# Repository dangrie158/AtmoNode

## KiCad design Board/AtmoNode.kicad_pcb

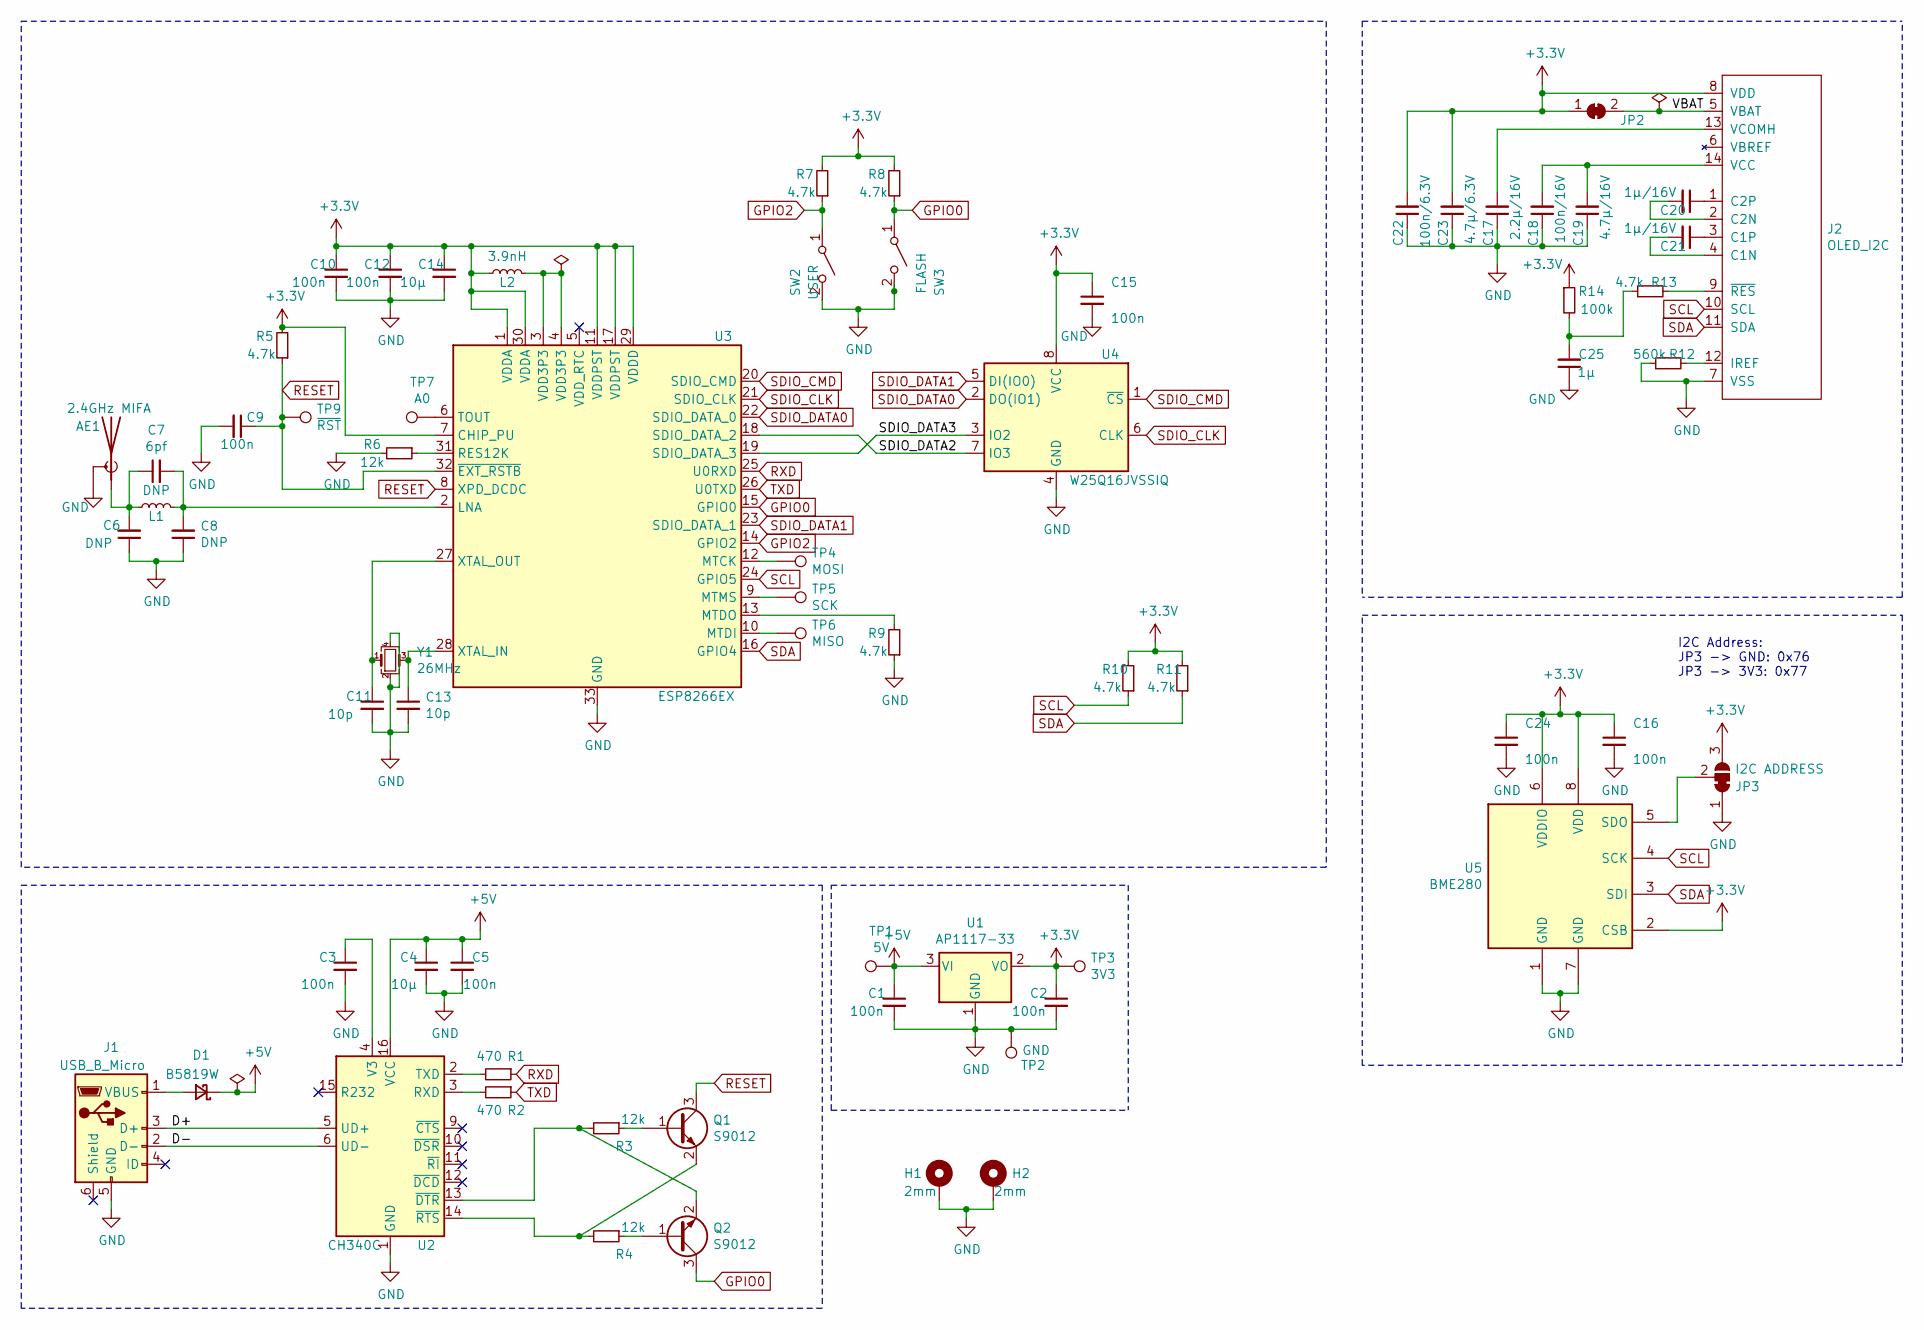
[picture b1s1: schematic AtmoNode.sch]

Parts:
AE1: 2.4GHz MIFA; Texas_SWRA117D_2.4GHz_Right
C1, C2, C3, C5, C9, C10, C12, C15, C16, C24: 100n; C_0402_1005Metric
C4, C14: 10µ; C_0805_2012Metric
C6, C8: DNP; C_0402_1005Metric
C7: 6pf; C_0402_1005Metric
C11, C13: 10p; C_0402_1005Metric
C17: 2.2µ/16V; C_0603_1608Metric
C18: 100n/16V; C_0402_1005Metric
C19: 4.7µ/16V; C_0603_1608Metric
C20, C21: 1µ/16V; C_0603_1608Metric
C22: 100n/6.3V; C_0402_1005Metric
C23: 4.7µ/6.3V; C_0603_1608Metric
C25: 1µ; C_0603_1608Metric
D1: B5819W; D_SOD-123
H1, H2: 2mm; MountingHole_2.2mm_M2_Pad_Via
J1: USB_B_Micro; USB_Micro-B_Amphenol_10118194_Horizontal
J2: OLED_I2C; WiseChip VG-6432TSWAG01
JP2: VDD-VBAT; SolderJumper-2_P1.3mm_Bridged_RoundedPad1.0x1.5mm
JP3: I2C ADDRESS; SolderJumper-3_P1.3mm_Bridged2Bar12_RoundedPad1.0x1.5mm
L1: DNP; L_0402_1005Metric_Pad0.77x0.64mm_HandSolder
L2: 3.9nH; L_0402_1005Metric_Pad0.77x0.64mm_HandSolder
Q1, Q2: S9012; SOT-23
R1, R2: 470; R_0402_1005Metric
R3, R4, R6: 12k; R_0402_1005Metric
R5, R7, R8, R9, R10, R11, R13: 4.7k; R_0402_1005Metric
R12: 560k; R_0603_1608Metric
R14: 100k; R_0402_1005Metric
SW2: USER; SW_SPST_CK_RS282G05A3
SW3: FLASH; SW_SPST_CK_RS282G05A3
TP1: 5V; TP1.0
TP2: GND; TP1.0
TP3: 3V3; TP1.0
TP4: MOSI; TP1.0
TP5: SCK; TP1.0
TP6: MISO; TP1.0
TP7: A0; TP1.0
TP9: ~RST; TP1.0
U1: AP1117-33; SOT-223-3_TabPin2
U2: CH340C; SOIC-16_3.9x9.9mm_P1.27mm
U3: ESP8266EX; QFN-32-1EP_5x5mm_P0.5mm_EP3.45x3.45mm
U4: W25Q16JVSSIQ; SOIC-8_5.23x5.23mm_P1.27mm
U5: BME280; Bosch_LGA-8_2.5x2.5mm_P0.65mm_ClockwisePinNumbering
Y1: 26MHz; Crystal_SMD_3225-4Pin_3.2x2.5mm

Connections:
+3V3: C2.1, C10.1, C12.1, C14.1, C15.1, C16.1, C22.2, C23.2, C24.1, J2.8 (VDD), JP2.1 (A), JP3.3 (B), L2.1, R5.2, R7.2, R8.2, R10.2, R11.2, R14.1, TP3.1, U1.2 (VO), U3.1 (VDDA), U3.7 (CHIP_PU), U3.11 (VDDPST), U3.17 (VDDPST), U3.29 (VDDD), U3.30 (VDDA), U4.8 (VCC), U5.2 (CSB), U5.6 (VDDIO), U5.8 (VDD)
+5V: C1.1, C4.1, C5.1, D1.1 (K), TP1.1, U1.3 (VI), U2.16 (VCC)
/D+: J1.3 (D+), U2.5 (UD+)
/D-: J1.2 (D-), U2.6 (UD-)
/SDIO_DATA2: U3.18 (SDIO_DATA_2), U4.7 (IO3)
/SDIO_DATA3: U3.19 (SDIO_DATA_3), U4.3 (IO2)
/VBAT: J2.5 (VBAT), JP2.2 (B)
GND: AE1.2 (Shield), C1.2, C2.2, C3.2, C4.2, C5.2, C6.1, C8.1, C9.2, C10.2, C11.2, C12.2, C13.2, C14.2, C15.2, C16.2, C17.1, C18.1, C19.1, C22.1, C23.1, C24.2, C25.1, H1.1, H2.1, J1.5 (GND), J2.7 (VSS), JP3.1 (A), R6.2, R9.1, R12.1, SW2.2 (B), SW3.2 (B), TP2.1, U1.1 (GND), U2.1 (GND), U3.33 (GND), U4.4 (GND), U5.1 (GND), U5.7 (GND), Y1.2, Y1.4
GPIO0: Q2.3 (C), R8.1, SW3.1 (A), U3.15 (GPIO0)
GPIO2: R7.1, SW2.1 (A), U3.14 (GPIO2)
unnamed: AE1.1 (A), C6.2, C7.1, L1.1
unnamed: C3.1, U2.4 (V3)
unnamed: C7.2, C8.2, L1.2, U3.2 (LNA)
unnamed: C11.1, U3.27 (XTAL_OUT), Y1.1
unnamed: C13.1, U3.28 (XTAL_IN), Y1.3
unnamed: C17.2, J2.13 (VCOMH)
unnamed: C18.2, C19.2, J2.14 (VCC)
unnamed: C20.1, J2.1 (C2P)
unnamed: C20.2, J2.2 (C2N)
unnamed: C21.1, J2.3 (C1P)
unnamed: C21.2, J2.4 (C1N)
unnamed: C25.2, R13.1, R14.2
unnamed: D1.2 (A), J1.1 (VBUS)
unnamed: J2.9 (~RES), R13.2
unnamed: J2.12 (IREF), R12.2
unnamed: JP3.2 (C), U5.5 (SDO)
unnamed: L2.2, U3.3 (VDD3P3), U3.4 (VDD3P3)
unnamed: Q1.1 (B), R3.1
unnamed: Q1.2 (E), R4.2, U2.14 (~RTS)
unnamed: Q2.1 (B), R4.1
unnamed: Q2.2 (E), R3.2, U2.13 (~DTR)
unnamed: R1.2, U2.2 (TXD)
unnamed: R2.2, U2.3 (RXD)
unnamed: R6.1, U3.31 (RES12K)
unnamed: R9.2, U3.13 (MTDO)
unnamed: TP4.1, U3.12 (MTCK)
unnamed: TP5.1, U3.9 (MTMS)
unnamed: TP6.1, U3.10 (MTDI)
unnamed: TP7.1, U3.6 (TOUT)
RESET: C9.1, Q1.3 (C), R5.1, TP9.1, U3.8 (XPD_DCDC), U3.32 (~EXT_RSTB)
RXD: R1.1, U3.25 (U0RXD)
SCL: J2.10 (SCL), R10.1, U3.24 (GPIO5), U5.4 (SCK)
SDA: J2.11 (SDA), R11.1, U3.16 (GPIO4), U5.3 (SDI)
SDIO_CLK: U3.21 (SDIO_CLK), U4.6 (CLK)
SDIO_CMD: U3.20 (SDIO_CMD), U4.1 (~CS)
SDIO_DATA0: U3.22 (SDIO_DATA_0), U4.2 (DO(IO1))
SDIO_DATA1: U3.23 (SDIO_DATA_1), U4.5 (DI(IO0))
TXD: R2.1, U3.26 (U0TXD)

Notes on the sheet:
I2C Address: JP3 -> GND: 0x76 JP3 -> 3V3: 0x77

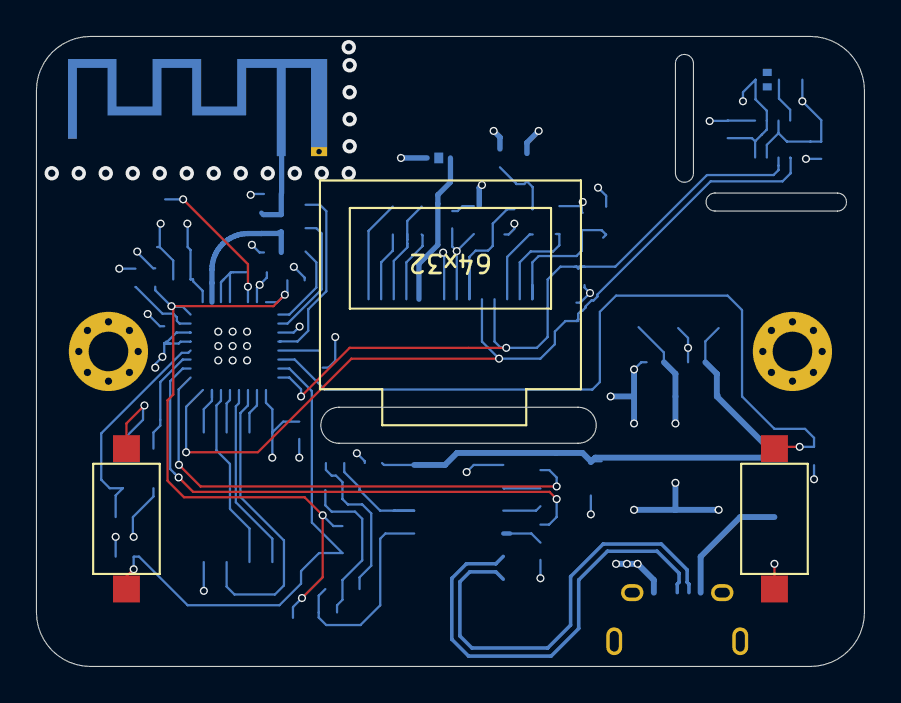
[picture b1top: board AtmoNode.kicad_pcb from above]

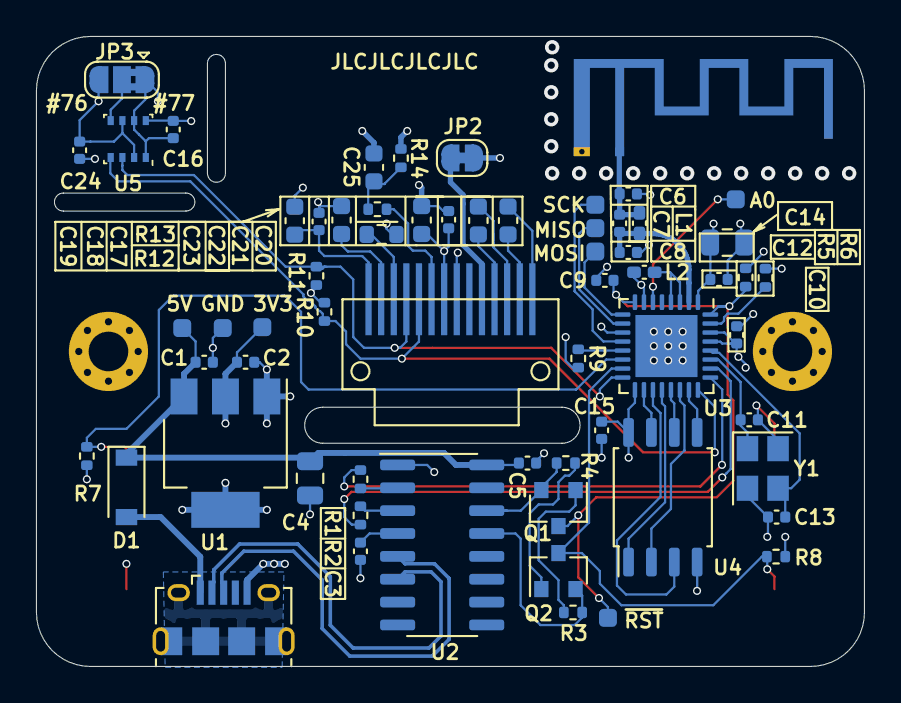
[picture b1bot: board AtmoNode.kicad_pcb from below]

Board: 4 copper layers, 46.0 x 35.0 mm, 67 parts (63 on the bottom side), 48 nets.

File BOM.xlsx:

Id | Designator | Footprint | Quantity | Comment | Supplier and ref
1 | R12 | 603 | 1 | 560k
2 | C4,C14 | 805 | 2 | 10u
3 | L1 | 0402.77x0.64mm_HandSolder | 1 | DNP
5 | U5 | Bosch_LGA-8_2.5x2.5mm_P0.65mm_ClockwisePinNumbering | 1 | BME280
6 | R11,R10,R9,R13,R8,R7,R5 | 402 | 7 | 4.7k
7 | C24,C15,C16,C12,C10,C9,C5,C3,C2,C1 | 402 | 10 | 100n 16V
9 | C20,C21 | 603 | 2 | 1u 16V
10 | L2 | 402 | 1 | 3.9nH
19 | Q2,Q1 | SOT-23 | 2 | S9012
20 | R14,R15 | 402 | 2 | 47k
21 | J2 | WiseChip VG-6432TSWAG01 | 1 | OLED_I2C
22 | R3,R6,R4 | 402 | 3 | 12k
23 | U2 | SOIC | 1 | CH340C
25 | C19 | 603 | 1 | 4.7u/16V
26 | C17 | 603 | 1 | 2.2u/16V
28 | R2,R1 | 402 | 2 | 470
29 | C22 | 402 | 1 | 100n 16V
30 | C18 | 402 | 1 | 100n 16V
31 | C13,C11 | 402 | 2 | 10p
32 | C8,C6 | 402 | 2 | DNP
33 | C7 | 402 | 1 | 6pf
35 | Y1 | 3225 | 1 | 26MHz
36 | Q4 | SOT-23 | 1 | FDN335N
37 | Q3 | SOT-23 | 1 | FDN338P
40 | U4 | SOIC-8 | 1 | W25Q16JVSSIQ
41 | U3 | QFN-32 | 1 | ESP8266EX
42 | U1 | SOT-223 | 1 | AP1117-33
45 | D1 | D_SOD-123 | 1 | B5819W
46 | C23 | 603 | 1 | 4.7u/6.3V

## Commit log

2020-12-25 added kicad project
2020-12-25 added ordered gerbers
2020-12-25 added gitignore for kicad files
2020-12-25 added firmware folder
2020-12-30 added files for Laser-cut Case
2020-12-30 added gcode for milling the case
2020-12-30 added OTA update functionality
2020-12-30 refactored firmware to use self hosted mqtt + influx + grafana
2023-02-21 added offset to calibrate BMS
